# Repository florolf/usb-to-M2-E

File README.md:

# USB ⇔ M.2-E

## Why?

I wanted an USB Bluetooth dongle with support for recent Bluetooth versions (and LE Isochronous Channels in particular, while still supporting Bluetooth Classic) with Linux support that isn't excessively painful, which rules out basically every off-the-shelf dongle in existence.

Intel WiFi cards have excellent Bluetooth support, but they come in the form of M.2 cards which are meant to be installed internally. The aim of this project was to answer the question whether those cards would still work if only the Bluetooth component (which uses USB, unlike the WiFi part which attaches through PCIe) was active. The answer turned out to be yes (see [below](#compatibilty) for known-working cards).

## What is it?

It's a simple PCB that contains:

 * An USB-C receptacle
 * A 5V → 3.3V voltage regulator
 * A M.2 E-key socket
 * Optionally a SUSCLK oscillator

Only the USB section of the M.2 interface is connected.

## Fabrication

This is a basic 1.6mm 2 layer board that should be manufacturable almost anywhere. I used JLCPCB, you can find the Gerbers in the [`generated/fab`](generated/fab/) directory and a BOM in [`generated/bom.csv`](generated/bom.csv).

## Compatibility

This section lists cards that are known to work with this adapter:

 * Intel Killer BE1750x (Bluetooth uses the `AUX` antenna)

Note that most Intel WiFi cards also come in a CNVio variant that uses the same connector, but uses it in a non-standard fashion. It is unknown if those cards would work with this adapter.

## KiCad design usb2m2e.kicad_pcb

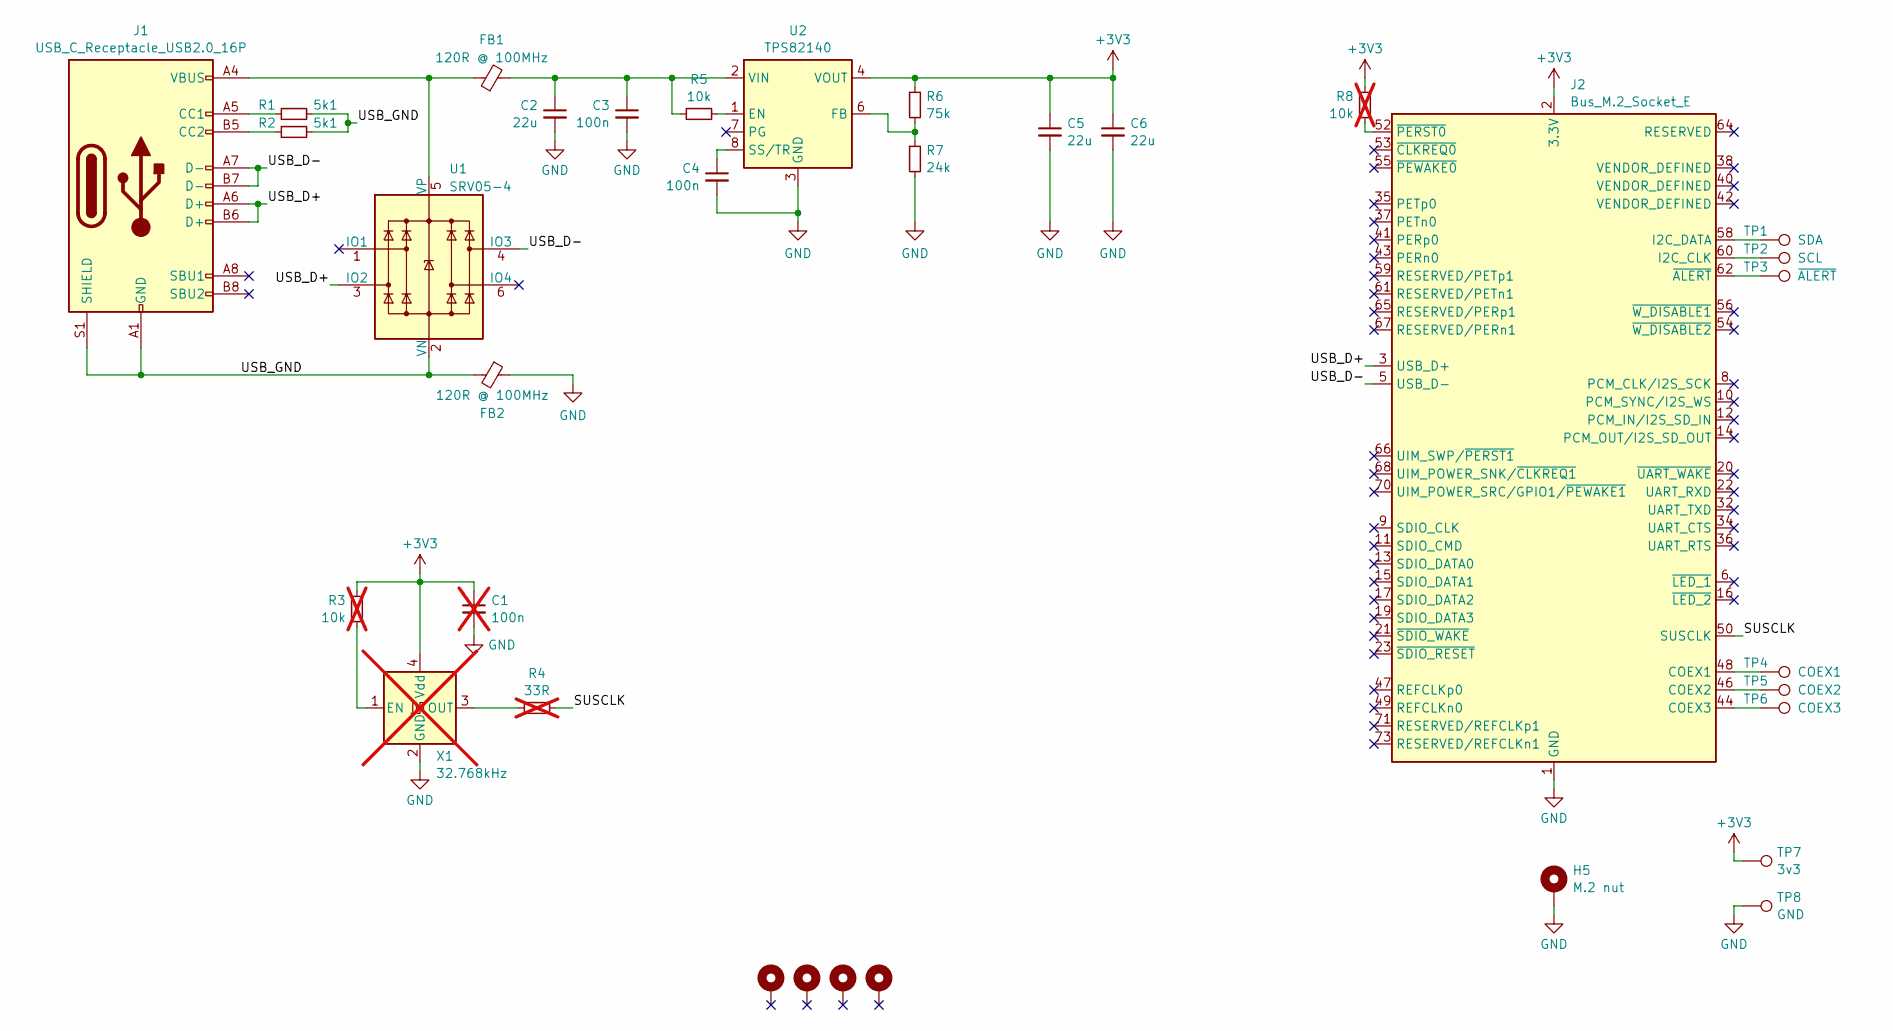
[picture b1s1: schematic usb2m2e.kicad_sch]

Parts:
C1: 100n; C_0402_1005Metric; not fitted
C2, C5, C6: 22u; C_1206_3216Metric
C3, C4: 100n; C_0402_1005Metric
FB1, FB2: 120R @ 100MHz; L_0805_2012Metric; MPN 2508051217Y6; Digikey 1934-1472-1-ND
H1, H2, H3, H4: MountingHole_Pad; MountingHole_2.7mm_M2.5_ISO14580_Pad
H5: M.2 nut; JAE_SM3ZS067Uxxx-NUT1; MPN SM3ZS067U410-NUT1-R1200; Digikey 670-2865-1-ND
J1: USB_C_Receptacle_USB2.0_16P; USB_C_Receptacle_HRO_TYPE-C-31-M-12
J2: Bus_M.2_Socket_E; JAE_SM3ZS067UxxM; MPN SM3ZS067U410AER1000; Digikey 670-2692-1-ND
R1, R2: 5k1; R_0402_1005Metric
R3, R8: 10k; R_0402_1005Metric; not fitted
R4: 33R; R_0402_1005Metric; not fitted
R5: 10k; R_0402_1005Metric
R6: 75k; R_0402_1005Metric
R7: 24k; R_0402_1005Metric
TP1: SDA; TestPoint_Pad_D1.5mm
TP2: SCL; TestPoint_Pad_D1.5mm
TP3: ~{ALERT}; TestPoint_Pad_D1.5mm
TP4: COEX1; TestPoint_Pad_D1.5mm
TP5: COEX2; TestPoint_Pad_D1.5mm
TP6: COEX3; TestPoint_Pad_D1.5mm
TP7: 3v3; TestPoint_Pad_D1.5mm
TP8: GND; TestPoint_Pad_D1.5mm
U1: SRV05-4; SOT-23-6; MPN SRV05-4L-TP; Digikey SRV05-4L-TPMSCT-ND
U2: TPS82140; Texas_SIL0008D_MicroSiP-8-1EP_2.8x3mm_P0.65mm_EP1.1x1.9mm_T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; MPN TPS82140SIL; Digikey 296-48215-1-ND
X1: 32.768kHz; Crystal_SMD_3225-4Pin_3.2x2.5mm; MPN ECS-327KE-TR; Digikey XC1751CT-ND; not fitted

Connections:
+3V3: C1.1, C5.1, C6.1, J2.2 (3.3V), J2.4 (3.3V), J2.72 (3.3V), J2.74 (3.3V), R3.1, R6.1, R8.1, TP7.1, U2.4 (VOUT), U2.5 (VOUT), X1.4 (Vdd)
/SUSCLK: J2.50 (SUSCLK), R4.2
/USB_D+: J1.A6 (D+), J1.B6 (D+), J2.3 (USB_D+), U1.3 (IO2)
/USB_D-: J1.A7 (D-), J1.B7 (D-), J2.5 (USB_D-), U1.4 (IO3)
/USB_GND: FB2.2, J1.A1 (GND), J1.A12 (GND), J1.B1 (GND), J1.B12 (GND), J1.S1 (SHIELD), R1.2, R2.2, U1.2 (VN)
GND: C1.2, C2.2, C3.2, C4.2, C5.2, C6.2, FB2.1, H5.1, J2.1 (GND), J2.7 (GND), J2.18 (GND), J2.33 (GND), J2.39 (GND), J2.45 (GND), J2.51 (GND), J2.57 (GND), J2.63 (GND), J2.69 (GND), J2.75 (GND), R7.2, TP8.1, U2.3 (GND), U2.9 (GND), X1.2 (GND)
unnamed: J1.A5 (CC1), R1.1
unnamed: J1.B5 (CC2), R2.1
unnamed: J2.48 (COEX1), TP4.1
unnamed: J2.46 (COEX2), TP5.1
unnamed: J2.44 (COEX3), TP6.1
unnamed: J2.60 (I2C_CLK), TP2.1
unnamed: J2.58 (I2C_DATA), TP1.1
unnamed: J2.62 (~ALERT), TP3.1
unnamed: J2.52 (~PERST0), R8.2
unnamed: FB1.1, J1.A4 (VBUS), J1.A9 (VBUS), J1.B4 (VBUS), J1.B9 (VBUS), U1.5 (VP)
unnamed: R5.2, U2.1 (EN)
unnamed: R6.2, R7.1, U2.6 (FB)
unnamed: C4.1, U2.8 (SS/TR)
unnamed: C2.1, C3.1, FB1.2, R5.1, U2.2 (VIN)
unnamed: R3.2, X1.1 (EN)
unnamed: R4.1, X1.3 (OUT)

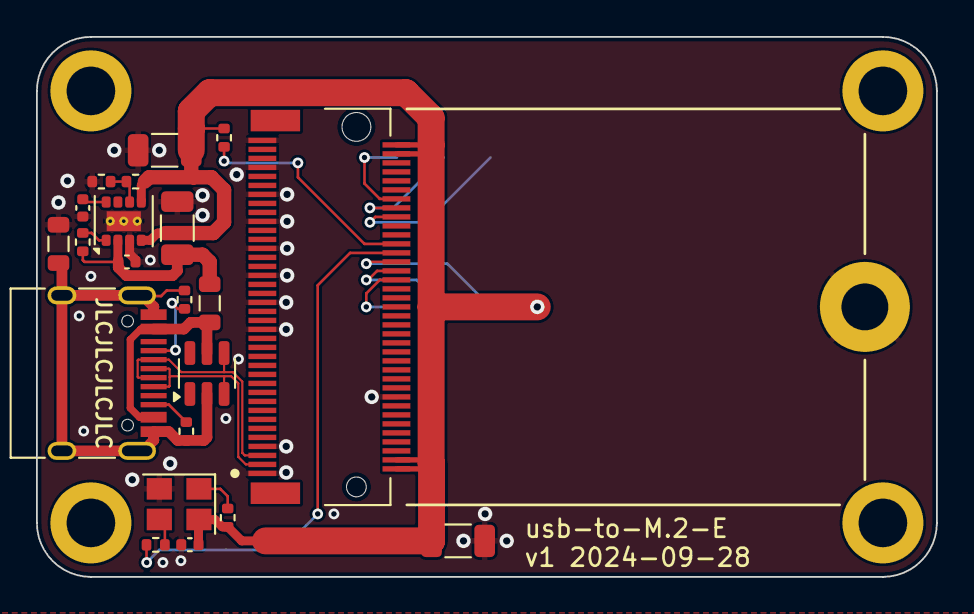
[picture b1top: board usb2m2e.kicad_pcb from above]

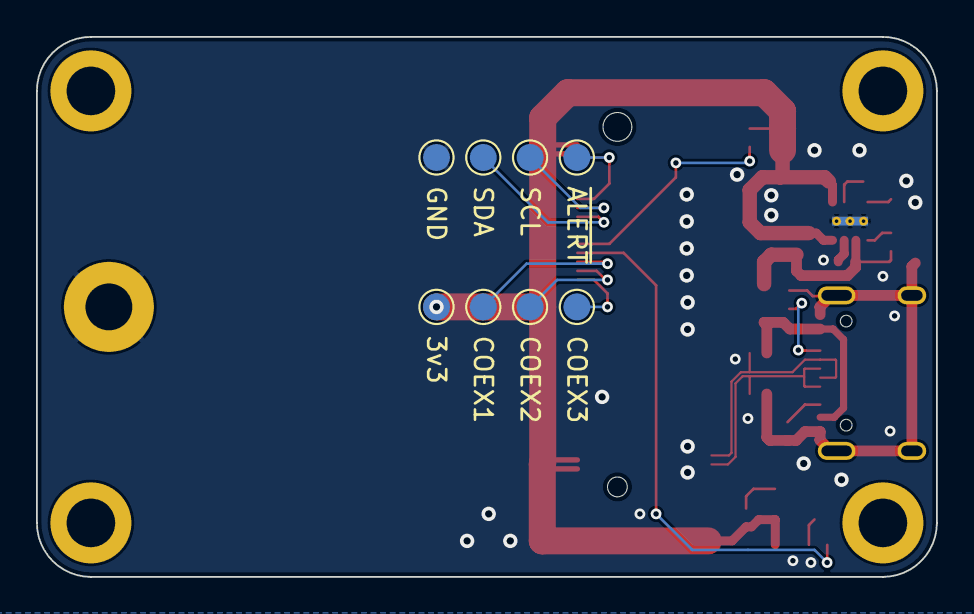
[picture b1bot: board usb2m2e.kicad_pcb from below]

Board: 2 copper layers, 50.0 x 30.0 mm, 34 parts (8 on the bottom side), 22 nets.

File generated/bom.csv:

"Reference","Value","Datasheet","Footprint","Qty","Digikey"
"J1","USB_C_Receptacle_USB2.0_16P","https://www.usb.org/sites/default/files/documents/usb_type-c.zip","Connector_USB:USB_C_Receptacle_HRO_TYPE-C-31-M-12","1",""
"C2,C5,C6","22u","~","Capacitor_SMD:C_1206_3216Metric","3",""
"C1,C3,C4","100n","~","Capacitor_SMD:C_0402_1005Metric","3",""
"R7","24k","~","Resistor_SMD:R_0402_1005Metric","1",""
"R6","75k","~","Resistor_SMD:R_0402_1005Metric","1",""
"R4","33R","~","Resistor_SMD:R_0402_1005Metric","1",""
"R3,R5,R8","10k","~","Resistor_SMD:R_0402_1005Metric","3",""
"R1,R2","5k1","~","Resistor_SMD:R_0402_1005Metric","2",""
"J2","Bus_M.2_Socket_E","https://www.jae.com/direct/topics/topics_file_download/?topi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","local:JAE_SM3ZS067UxxM","1","670-2692-1-ND"
"U2","TPS82140","http://www.ti.com/lit/ds/symlink/tps82140.pdf","Package_LGA:Texas_SIL0008D_MicroSiP-8-1EP_2.8x3mm_P0.65mm_EP1.1x1.9mm_ThermalVias","1","296-48215-1-ND"
"X1","32.768kHz","https://ecsxtal.com/store/pdf/ECS_327KE.pdf","Crystal:Crystal_SMD_3225-4Pin_3.2x2.5mm","1","XC1751CT-ND"
"U1","SRV05-4","","Package_TO_SOT_SMD:SOT-23-6","1","SRV05-4L-TPMSCT-ND"
"FB1,FB2","120R @ 100MHz","https://www.fair-rite.com/wp-content/themes/fair-rite/print_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","Inductor_SMD:L_0805_2012Metric","2","1934-1472-1-ND"

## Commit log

2024-12-01 import for GitHub
